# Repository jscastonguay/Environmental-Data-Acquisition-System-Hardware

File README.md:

# Environmental Data Acquisition System - Hardware

TBD

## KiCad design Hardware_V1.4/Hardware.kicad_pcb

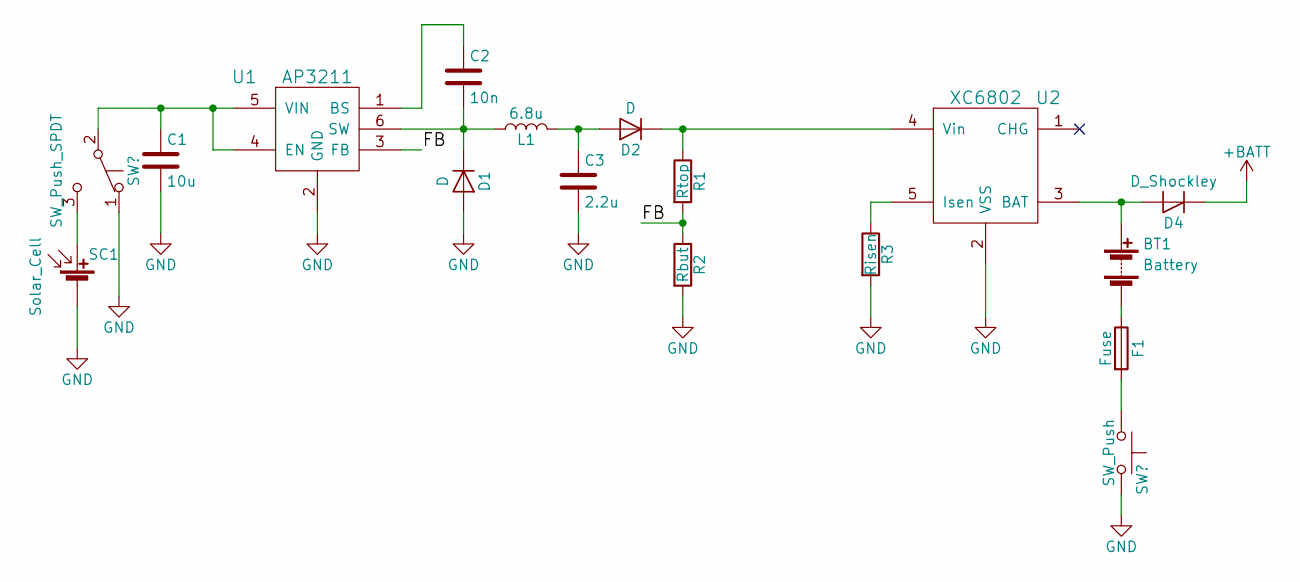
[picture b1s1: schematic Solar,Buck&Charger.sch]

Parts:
BT1: Battery; Pin_Header_Straight_1x02_Pitch2.54mm
C1: 10u; C_0805
C2: 10n; C_0805
C3: 2.2u; C_0805
D1, D2: D; D_0805
D4: D_Shockley; DPAK-3
F1: Fuse; Fuse_0679H
L1: 6.8u; L_0805
R1: Rtop; R_0805
R2: Rbut; R_0805
R3: Risen; R_0805
SC1: Solar_Cell; Pin_Header_Straight_1x02_Pitch2.54mm
U1: AP3211; SOT-23-6
U2: XC6802; SOT-23-5

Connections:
+BATT: D4.1 (K); also elsewhere on the board
/Solar,Buck&Charger/FB: R1.2, R2.1, U1.3 (FB)
GND: C1.2, C3.2, D1.2 (A), F1.2, R2.2, R3.2, SC1.2 (-), U1.2 (GND), U2.2 (VSS); also elsewhere on the board
unnamed: BT1.1 (+), D4.2 (A), U2.3 (BAT)
unnamed: BT1.2 (-), F1.1
unnamed: C2.1, U1.1 (BS)
unnamed: C2.2, D1.1 (K), L1.1, U1.6 (SW)
unnamed: C3.1, D2.2 (A), L1.2
unnamed: D2.1 (K), R1.1, U2.4 (Vin)
unnamed: R3.1, U2.5 (Isen)

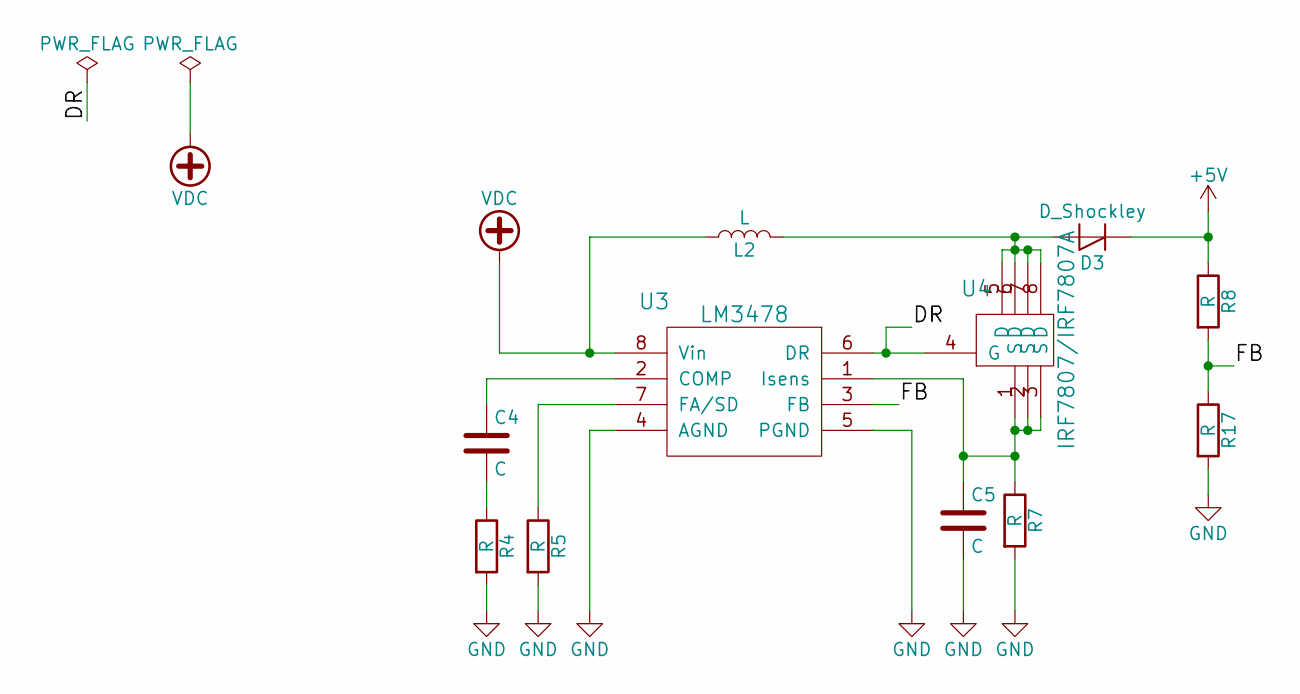
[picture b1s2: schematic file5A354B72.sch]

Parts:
C4, C5: C; C_0805
D3: D_Shockley; DPAK-3
L2: L; L_0805
R4, R5, R8, R17: R; R_0805
R7: R; R_2010
U3: LM3478; SOIC-8_3.9x4.9mm_Pitch1.27mm
U4: IRF7807/IRF7807A; SO-8_5.3x6.2mm_Pitch1.27mm

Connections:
+5V: D3.1 (K), R8.1; also elsewhere on the board
/Boost/DR: U3.6 (DR), U4.4 (G)
/Boost/FB: R8.2, R17.1, U3.3 (FB)
GND: C5.2, R4.2, R5.2, R7.2, R17.2, U3.4 (AGND), U3.5 (PGND); also elsewhere on the board
unnamed: C4.1, U3.2 (COMP)
unnamed: C4.2, R4.1
unnamed: C5.1, R7.1, U3.1 (Isens), U4.1 (S), U4.2 (S), U4.3 (S)
unnamed: D3.2 (A), L2.2, U4.5 (D), U4.6 (D), U4.7 (D), U4.8 (D)
unnamed: R5.1, U3.7 (FA/SD)
VDC: L2.1, U3.8 (Vin)

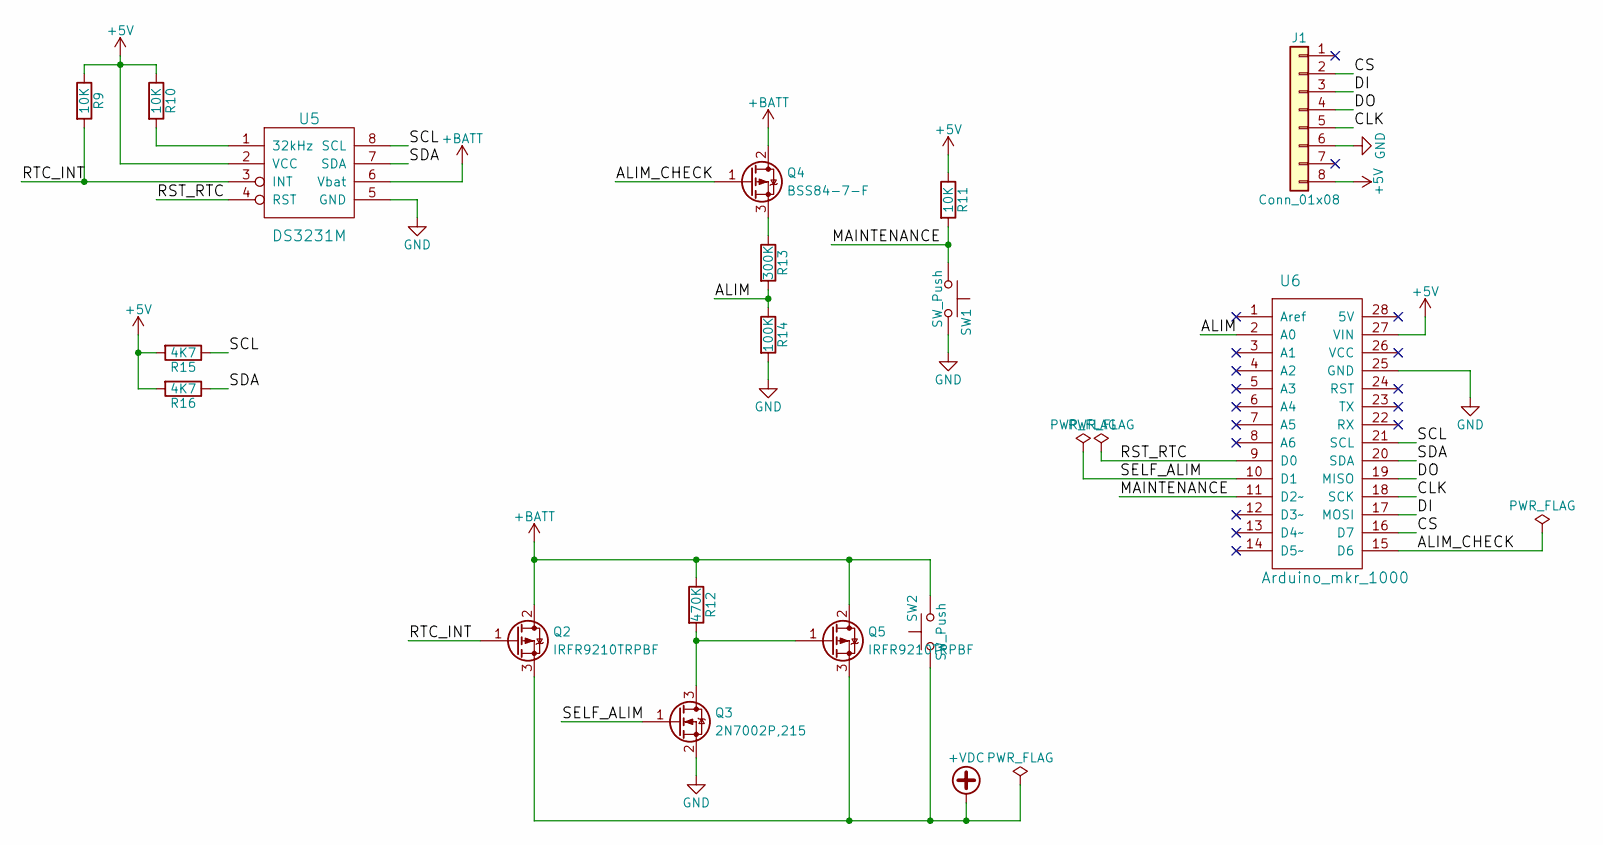
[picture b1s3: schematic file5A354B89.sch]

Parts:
J1: Conn_01x08; MicroSD_card_breakout_board
Q2, Q5: IRFR9210TRPBF; DPAK-3
Q3: 2N7002P,215; SOT-23
Q4: BSS84-7-F; SOT-23
R9, R10, R11: 10K; R_0805
R12: 470K; R_0805
R13: 300K; R_0805
R14: 100K; R_0805
R15, R16: 4K7; R_0805
SW1, SW2: SW_Push; SW_Tactile_SPST_Angled_PTS645Vx39-2LFS
U5: DS3231M; SOIC-8_3.9x4.9mm_Pitch1.27mm
U6: Arduino_mkr_1000; Arduino_MKR_GSM_1400

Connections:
+5V: J1.8, R9.1, R10.1, R11.1, R15.2, R16.2, U5.2 (VCC), U6.27 (VIN); also elsewhere on the board
+BATT: Q2.2 (D), Q4.2 (D), Q5.2 (D), R12.1, SW2.2, U5.6 (Vbat); also elsewhere on the board
+VDC: Q2.3 (S), Q5.3 (S), SW2.1
/mcu,rtc&sensor/ALIM: R13.2, R14.1, U6.2 (A0)
/mcu,rtc&sensor/ALIM_CHECK: Q4.1 (G), U6.15 (D6)
/mcu,rtc&sensor/CLK: J1.5, U6.18 (SCK)
/mcu,rtc&sensor/CS: J1.2, U6.16 (D7)
/mcu,rtc&sensor/DI: J1.3, U6.17 (MOSI)
/mcu,rtc&sensor/DO: J1.4, U6.19 (MISO)
/mcu,rtc&sensor/MAINTENANCE: R11.2, SW1.1, U6.11 (D2~~)
/mcu,rtc&sensor/RST_RTC: U5.4 (RST), U6.9 (D0)
/mcu,rtc&sensor/RTC_INT: Q2.1 (G), R9.2, U5.3 (INT)
/mcu,rtc&sensor/SCL: R15.1, U5.8 (SCL), U6.21 (SCL)
/mcu,rtc&sensor/SDA: R16.1, U5.7 (SDA), U6.20 (SDA)
/mcu,rtc&sensor/SELF_ALIM: Q3.1 (G), U6.10 (D1)
GND: J1.6, Q3.2 (S), R14.2, SW1.2, U5.5 (GND), U6.25 (GND); also elsewhere on the board
unnamed: Q3.3 (D), Q5.1 (G), R12.2
unnamed: Q4.3 (S), R13.1
unnamed: R10.2, U5.1 (32kHz)

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
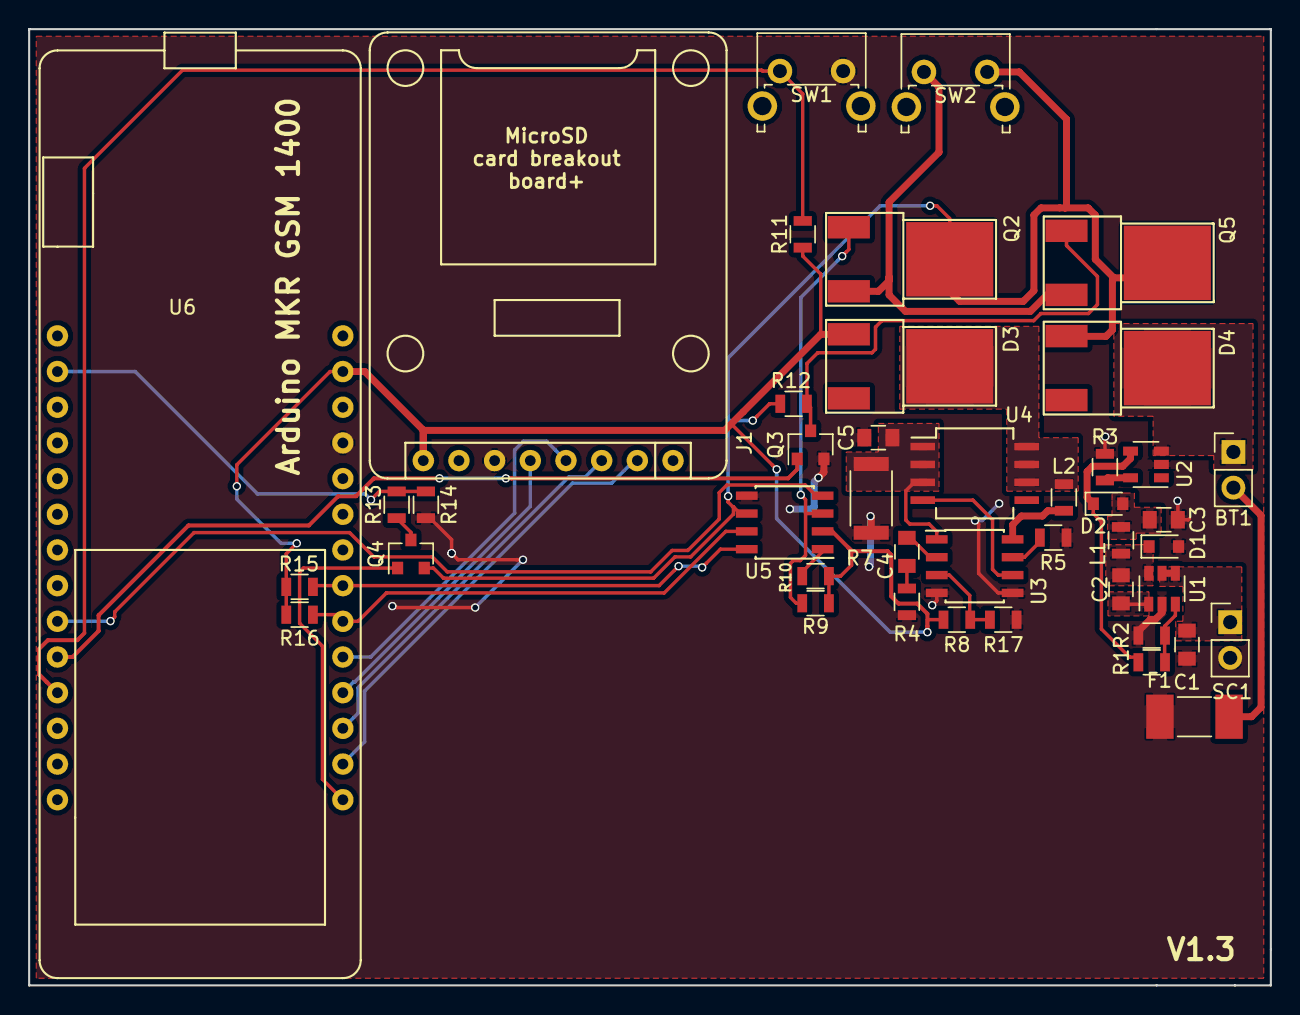
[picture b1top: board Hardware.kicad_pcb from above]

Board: 2 copper layers, 88.4 x 68.1 mm, 43 parts (0 on the bottom side), 36 nets.

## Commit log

2017-12-26 Add version 1.1 from Nicolas.
2017-12-29 V1.4 upload by Nicolas
